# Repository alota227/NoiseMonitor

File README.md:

# NoiseMonitor
To design a  noise monitoring system that is able to detect and localize the noise levels in an area and analyze the data obtained through the cloud. The system will have several (2-3) nodes that can communicate with each other to analyze the data accurately. The data will be classified through an auto-map system that can identify the low/high level noise areas in real-time. The device is a solution that can solve the issues and concerns of noise pollution in Saskatchewan.

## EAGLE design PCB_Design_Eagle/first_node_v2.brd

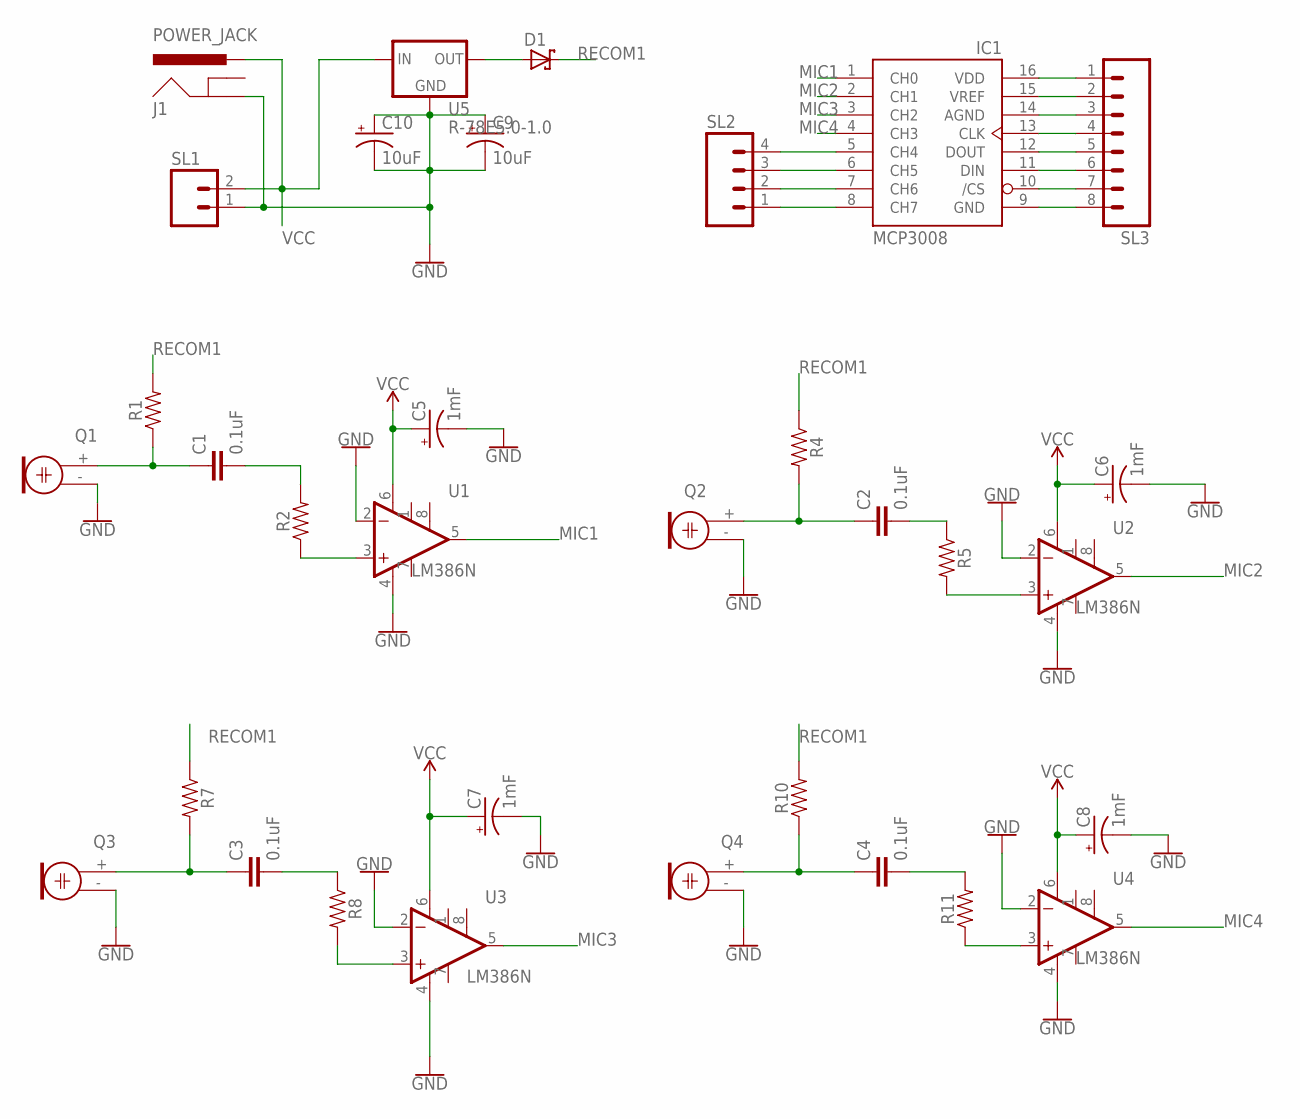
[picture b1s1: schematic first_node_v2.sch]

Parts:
C1, C2, C3, C4: 0.1uF; CAP-PTH-SMALL-KIT
C5, C6, C7, C8: 1mF; CPOL-RADIAL-5MM-10MM
C9, C10: 10uF; CPOL-RADIAL-2.5MM-5MM
D1: SCHOTTKY-DIODECB429-17; CB429-17
IC1: MCP3008; DIL16
J1: POWER_JACK; POWER_JACK_PTH
Q1, Q2, Q3, Q4: ELECTRET; 9.7ELECTRET
R1, R2, R4, R5, R7, R8, R10, R11: AXIAL-0.3
SL1: M02; 02P
SL2: M04; 04P
SL3: M08; 08P
U1, U2, U3, U4: LM386N; DIP08
U5: R-78E5.0-1.0; DC-DC_CONVERTER_78XX

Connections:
GND: C5.-, C6.-, C7.-, C8.-, C9.1 (+), C9.2 (-), C10.1 (+), C10.2 (-), J1.GND, Q1.- (1), Q2.- (1), Q3.- (1), Q4.- (1), SL1.1, U1.2 (-IN), U1.4 (V-), U2.2 (-IN), U2.4 (V-), U3.2 (-IN), U3.4 (V-), U4.2 (-IN), U4.4 (V-), U5.GND
MIC1: IC1.1 (CH0), U1.5 (OUT)
MIC2: IC1.2 (CH1), U2.5 (OUT)
MIC3: IC1.3 (CH2), U3.5 (OUT)
MIC4: IC1.4 (CH3), U4.5 (OUT)
unnamed: C1.1, Q1.+ (2), R1.P$1 (1)
unnamed: C1.2, R2.P$2 (2)
unnamed: C2.1, Q2.+ (2), R4.P$2 (2)
unnamed: C2.2, R5.P$1 (1)
unnamed: C3.1, Q3.+ (2), R7.P$2 (2)
unnamed: C4.1, Q4.+ (2), R10.P$1 (1)
unnamed: C3.2, R8.P$1 (1)
unnamed: C4.2, R11.P$2 (2)
unnamed: IC1.5 (CH4), SL2.4
unnamed: R8.P$2 (2), U3.3 (+IN)
unnamed: IC1.6 (CH5), SL2.3
unnamed: D1.A, U5.VOUT (OUT)
unnamed: IC1.7 (CH6), SL2.2
unnamed: IC1.8 (CH7), SL2.1
unnamed: IC1.16 (VDD), SL3.1
unnamed: IC1.15 (VREF), SL3.2
unnamed: IC1.14 (AGND), SL3.3
unnamed: IC1.13 (CLK), SL3.4
unnamed: IC1.12 (DOUT), SL3.5
unnamed: IC1.11 (DIN), SL3.6
unnamed: IC1.10 (/CS), SL3.7
unnamed: IC1.9 (GND), SL3.8
unnamed: R2.P$1 (1), U1.3 (+IN)
unnamed: R11.P$1 (1), U4.3 (+IN)
unnamed: R5.P$2 (2), U2.3 (+IN)
RECOM1: D1.C, R1.P$2 (2), R4.P$1 (1), R7.P$1 (1), R10.P$2 (2)
VCC: C5.+, C6.+, C7.+, C8.+, J1.PWR, SL1.2, U1.6 (V+), U2.6 (V+), U3.6 (V+), U4.6 (V+), U5.VIN (IN)

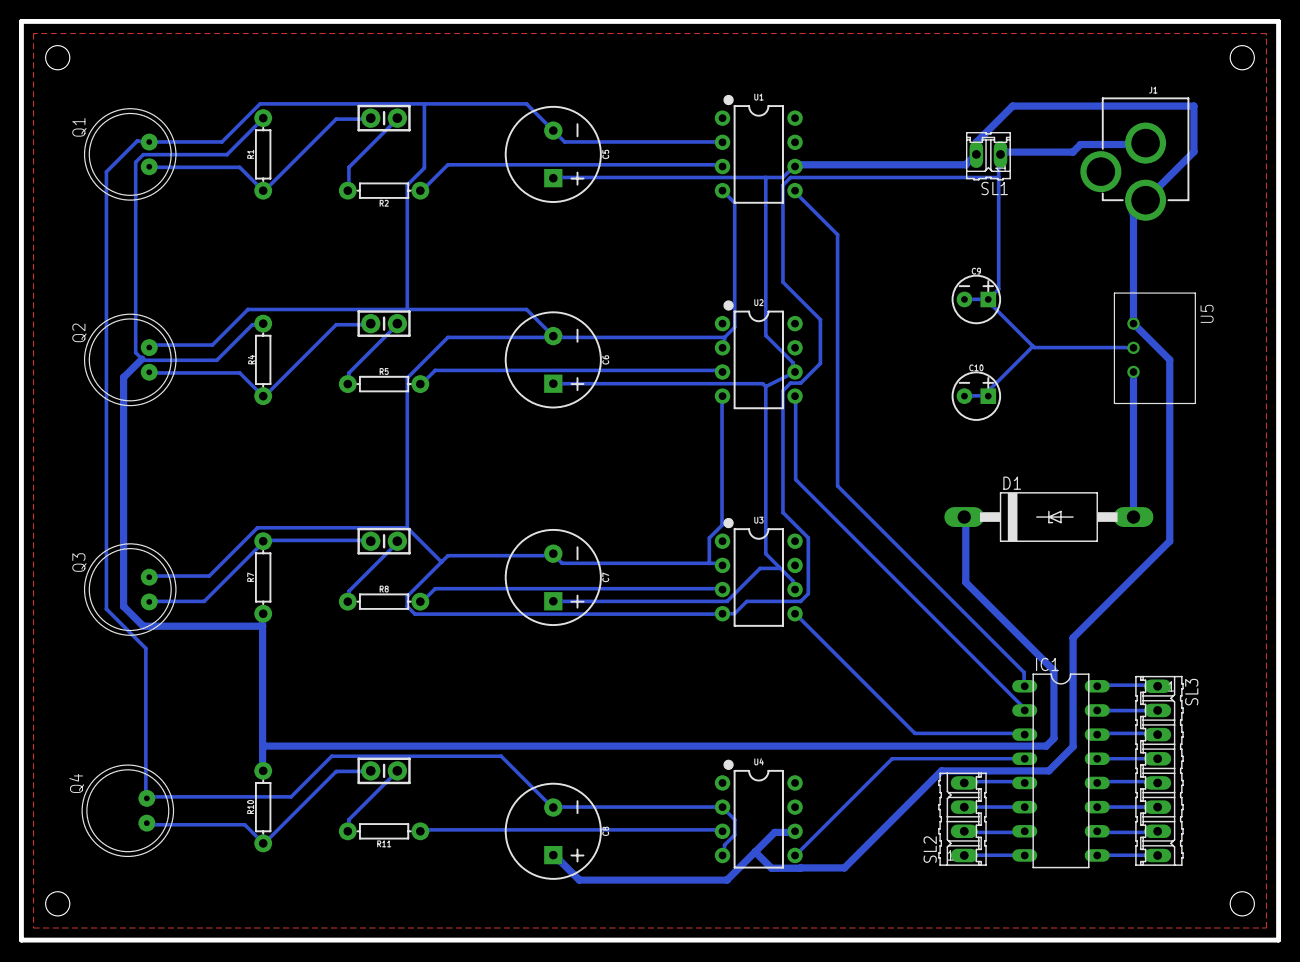
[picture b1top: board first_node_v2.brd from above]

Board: 2 copper layers, 132.1 x 96.5 mm, 33 parts (0 on the bottom side), 32 nets.

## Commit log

2019-01-11 Create Test_HTMLcode_Draft1
2019-01-11 Create Test_HTMLcode_Draft2_withoutPHP
2019-01-11 Add files via upload
    For initial testing purposes
2019-01-18 Add files via upload
    Initial PCB design of an individual node
2019-01-24 Create Webserver_Testing
2019-01-24 Create new-folder
2019-01-24 Create Webserver_Testing_v1
2019-01-31 Create PCB_Design
2019-01-31 Rename PCB_Design to PCB_Design_Eagle/design.txt
2019-01-31 Add files via upload
    gerber file
2019-02-19 cleaned
2019-03-07 Create Temp_Humidity_To_Website
2019-03-17 Create Webserver
2019-03-25 Create Data_To_Website

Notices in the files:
parts and their libraries:
SparkFun-Capacitors: Licensing: Creative Commons ShareAlike 4.0 International - https://creativecommons.org/licenses/by-sa/4.0
